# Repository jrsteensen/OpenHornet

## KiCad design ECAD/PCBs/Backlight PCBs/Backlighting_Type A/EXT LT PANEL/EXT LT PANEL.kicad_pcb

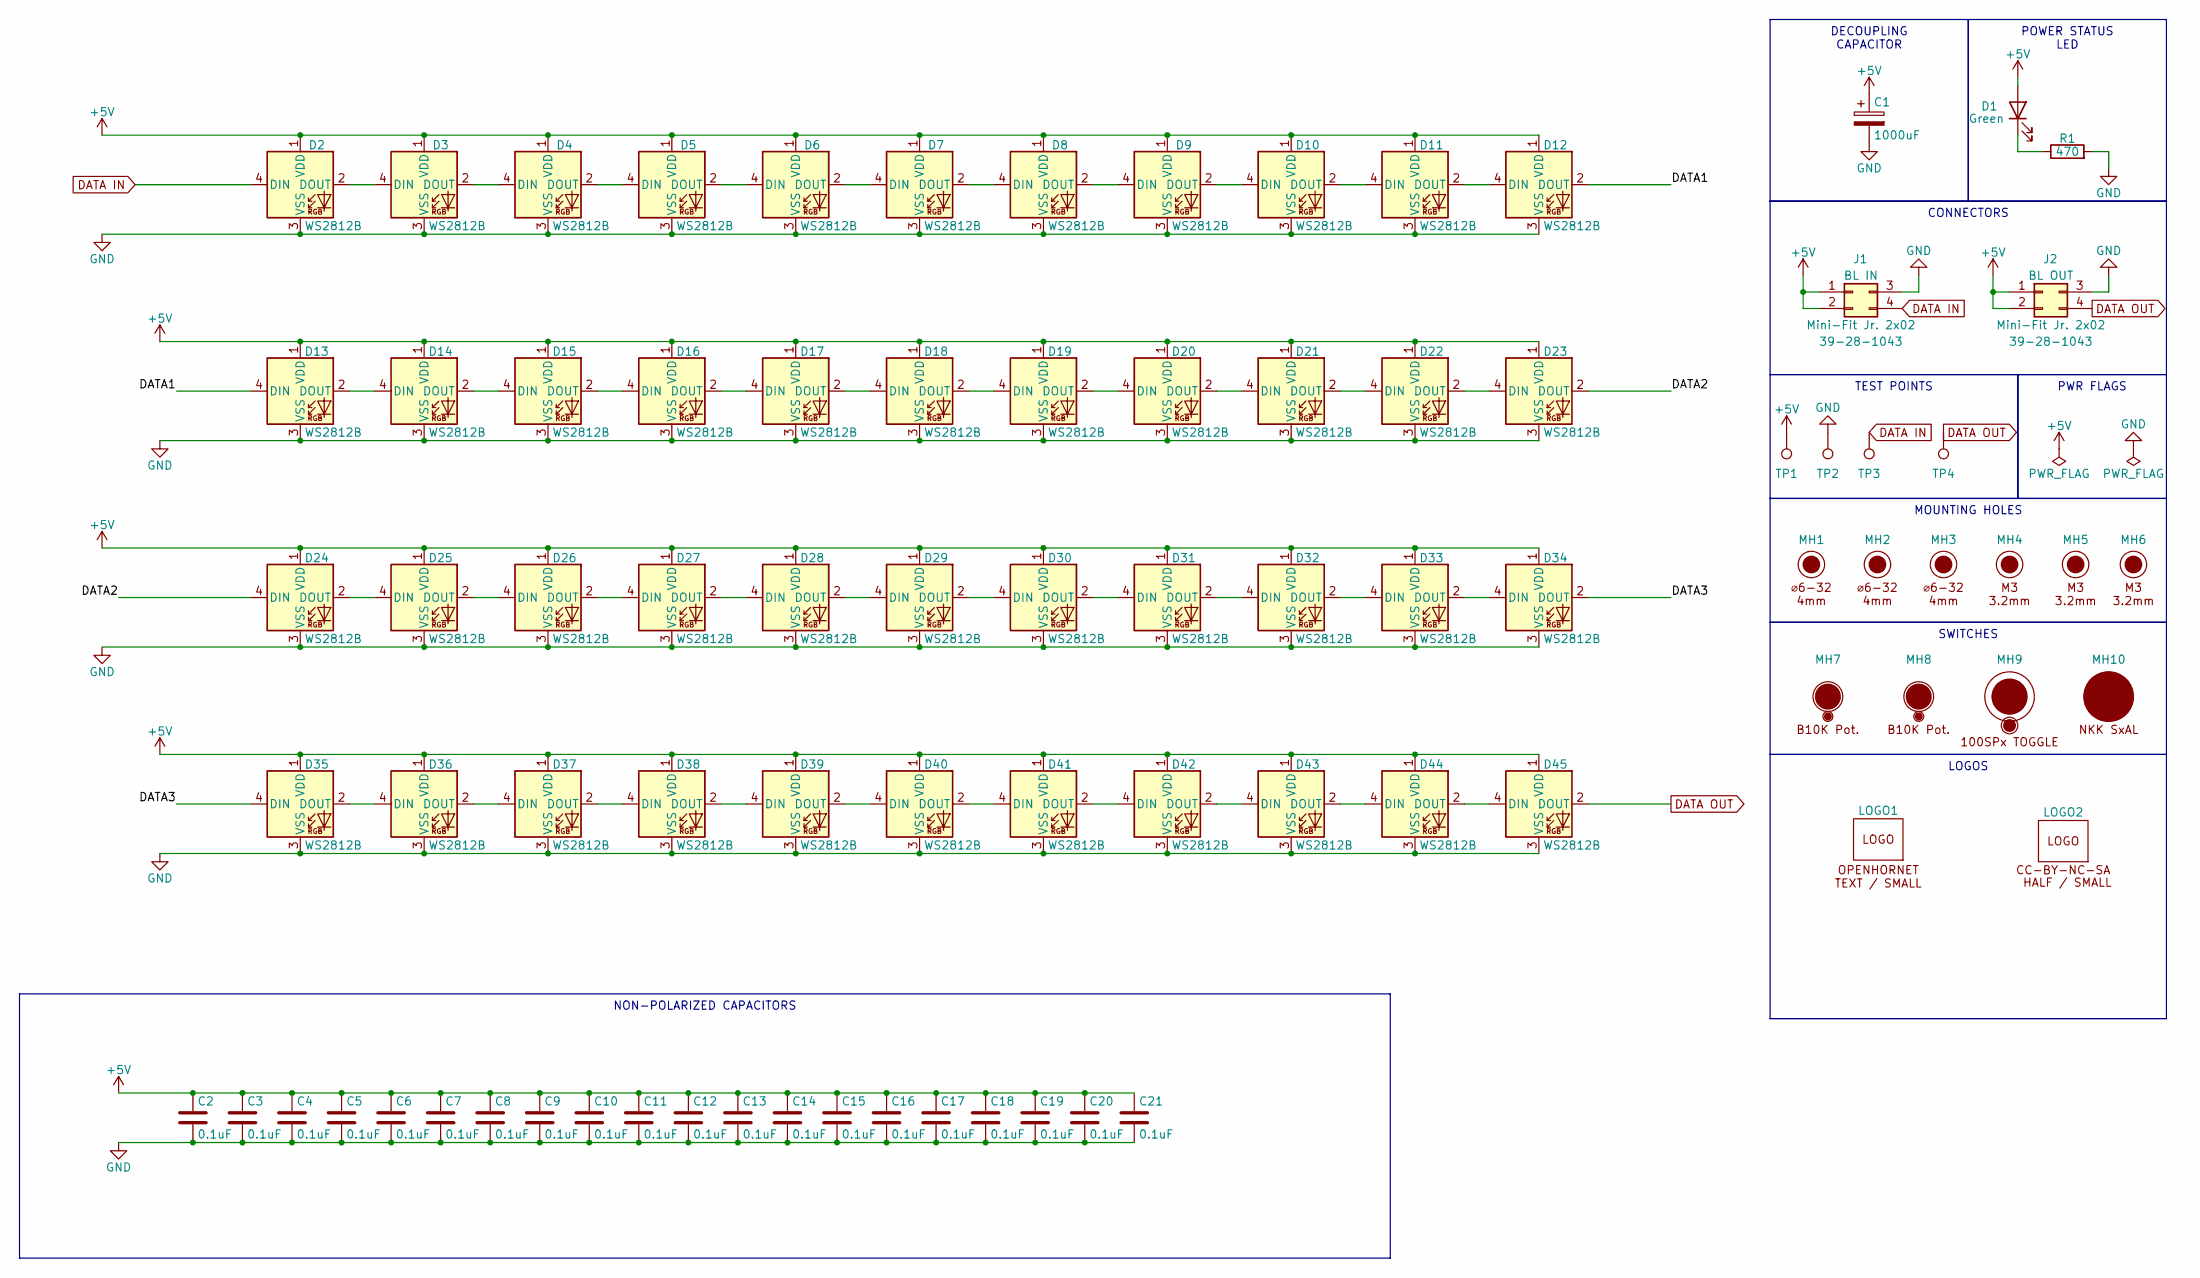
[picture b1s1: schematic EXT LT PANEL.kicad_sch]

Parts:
C1: 1000uF; CP_Elec_8x10; Manufacturer PN UWT0J102MNL1GS; LCSC C445083
C2, C3, C4, C5, C6, C7, C8, C9, C10, C11, C12, C13, C14, C15, C16, C17, C18, C19, C20, C21: 0.1uF; C_0603_1608Metric; Manufacturer PN CC0603KRX7R9BB104; LCSC C14663
D1: Green; LED_D3.0mm; Manufacturer PN 151031VS06000
D2, D3, D4, D5, D6, D7, D8, D9, D10, D11, D12, D13, D14, D15, D16, D17, D18, D19, D20, D21, D22, D23, D24, D25, D26, D27, D28, D29, D30, D31, D32, D33, D34, D35, D36, D37, D38, D39, D40, D41, D42, D43, D44, D45: WS2812B; LED_WS2812B_PLCC4_5.0x5.0mm_P3.2mm; Manufacturer PN WS2812B; LCSC C2761795
J1, J2: Mini-Fit Jr. 2x02; Molex_Mini-Fit_Jr_5566-04A_2x02_P4.20mm_Vertical; Manufacturer PN 39-28-1043; LCSC C293502
LOGO1: LOGO; LOGO_OH_Text_Small
LOGO2: LOGO; LOGO_CC-BY-NC-SA_Half_Small
MH1, MH2, MH3: 6x32 / 4mm; MountingHole_6-32_PHS
MH4, MH5, MH6: M3 / 3.2mm; MountingHole_3.2mm_M3_DIN965
MH7, MH8: Pot_B10K; BR10K_Pot_11mm_x_11mm; Manufacturer PN P0915N-FC20BR10K
MH9: Switch_100SPx; 100SPX_Toggle_13mm_x_18mm
MH10: Switch_NKK SxAL; SxAL_Toggle_13x13mm; Manufacturer PN SxAL
R1: 470; R_0603_1608Metric; Manufacturer PN 0603WAF4700T5E; LCSC C23179
TP1, TP2, TP3, TP4: TestPoint; TestPoint_THTPad_D1.5mm_Drill0.7mm

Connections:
+5V: C1.1, C2.1, C3.1, C4.1, C5.1, C6.1, C7.1, C8.1, C9.1, C10.1, C11.1, C12.1, C13.1, C14.1, C15.1, C16.1, C17.1, C18.1, C19.1, C20.1, C21.1, D1.2 (A), D2.1 (VDD), D3.1 (VDD), D4.1 (VDD), D5.1 (VDD), D6.1 (VDD), D7.1 (VDD), D8.1 (VDD), D9.1 (VDD), D10.1 (VDD), D11.1 (VDD), D12.1 (VDD), D13.1 (VDD), D14.1 (VDD), D15.1 (VDD), D16.1 (VDD), D17.1 (VDD), D18.1 (VDD), D19.1 (VDD), D20.1 (VDD), D21.1 (VDD), D22.1 (VDD), D23.1 (VDD), D24.1 (VDD), D25.1 (VDD), D26.1 (VDD), D27.1 (VDD), D28.1 (VDD), D29.1 (VDD), D30.1 (VDD), D31.1 (VDD), D32.1 (VDD), D33.1 (VDD), D34.1 (VDD), D35.1 (VDD), D36.1 (VDD), D37.1 (VDD), D38.1 (VDD), D39.1 (VDD), D40.1 (VDD), D41.1 (VDD), D42.1 (VDD), D43.1 (VDD), D44.1 (VDD), D45.1 (VDD), J1.1, J1.2 (Pin_3), J2.1, J2.2 (Pin_3), TP1.1
/DATA1: D12.2 (DOUT), D13.4 (DIN)
/DATA2: D23.2 (DOUT), D24.4 (DIN)
/DATA3: D34.2 (DOUT), D35.4 (DIN)
DATA IN: D2.4 (DIN), J1.4, TP3.1
DATA OUT: D45.2 (DOUT), J2.4, TP4.1
GND: C1.2, C2.2, C3.2, C4.2, C5.2, C6.2, C7.2, C8.2, C9.2, C10.2, C11.2, C12.2, C13.2, C14.2, C15.2, C16.2, C17.2, C18.2, C19.2, C20.2, C21.2, D2.3 (VSS), D3.3 (VSS), D4.3 (VSS), D5.3 (VSS), D6.3 (VSS), D7.3 (VSS), D8.3 (VSS), D9.3 (VSS), D10.3 (VSS), D11.3 (VSS), D12.3 (VSS), D13.3 (VSS), D14.3 (VSS), D15.3 (VSS), D16.3 (VSS), D17.3 (VSS), D18.3 (VSS), D19.3 (VSS), D20.3 (VSS), D21.3 (VSS), D22.3 (VSS), D23.3 (VSS), D24.3 (VSS), D25.3 (VSS), D26.3 (VSS), D27.3 (VSS), D28.3 (VSS), D29.3 (VSS), D30.3 (VSS), D31.3 (VSS), D32.3 (VSS), D33.3 (VSS), D34.3 (VSS), D35.3 (VSS), D36.3 (VSS), D37.3 (VSS), D38.3 (VSS), D39.3 (VSS), D40.3 (VSS), D41.3 (VSS), D42.3 (VSS), D43.3 (VSS), D44.3 (VSS), D45.3 (VSS), J1.3 (Pin_2), J2.3 (Pin_2), R1.2, TP2.1
unnamed: D1.1 (K), R1.1
unnamed: D2.2 (DOUT), D3.4 (DIN)
unnamed: D3.2 (DOUT), D4.4 (DIN)
unnamed: D4.2 (DOUT), D5.4 (DIN)
unnamed: D5.2 (DOUT), D6.4 (DIN)
unnamed: D6.2 (DOUT), D7.4 (DIN)
unnamed: D7.2 (DOUT), D8.4 (DIN)
unnamed: D8.2 (DOUT), D9.4 (DIN)
unnamed: D9.2 (DOUT), D10.4 (DIN)
unnamed: D10.2 (DOUT), D11.4 (DIN)
unnamed: D11.2 (DOUT), D12.4 (DIN)
unnamed: D13.2 (DOUT), D14.4 (DIN)
unnamed: D14.2 (DOUT), D15.4 (DIN)
unnamed: D15.2 (DOUT), D16.4 (DIN)
unnamed: D16.2 (DOUT), D17.4 (DIN)
unnamed: D17.2 (DOUT), D18.4 (DIN)
unnamed: D18.2 (DOUT), D19.4 (DIN)
unnamed: D19.2 (DOUT), D20.4 (DIN)
unnamed: D20.2 (DOUT), D21.4 (DIN)
unnamed: D21.2 (DOUT), D22.4 (DIN)
unnamed: D22.2 (DOUT), D23.4 (DIN)
unnamed: D24.2 (DOUT), D25.4 (DIN)
unnamed: D25.2 (DOUT), D26.4 (DIN)
unnamed: D26.2 (DOUT), D27.4 (DIN)
unnamed: D27.2 (DOUT), D28.4 (DIN)
unnamed: D28.2 (DOUT), D29.4 (DIN)
unnamed: D29.2 (DOUT), D30.4 (DIN)
unnamed: D30.2 (DOUT), D31.4 (DIN)
unnamed: D31.2 (DOUT), D32.4 (DIN)
unnamed: D32.2 (DOUT), D33.4 (DIN)
unnamed: D33.2 (DOUT), D34.4 (DIN)
unnamed: D35.2 (DOUT), D36.4 (DIN)
unnamed: D36.2 (DOUT), D37.4 (DIN)
unnamed: D37.2 (DOUT), D38.4 (DIN)
unnamed: D38.2 (DOUT), D39.4 (DIN)
unnamed: D39.2 (DOUT), D40.4 (DIN)
unnamed: D40.2 (DOUT), D41.4 (DIN)
unnamed: D41.2 (DOUT), D42.4 (DIN)
unnamed: D42.2 (DOUT), D43.4 (DIN)
unnamed: D43.2 (DOUT), D44.4 (DIN)
unnamed: D44.2 (DOUT), D45.4 (DIN)

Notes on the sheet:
DECOUPLING CAPACITOR
TEST POINTS
POWER STATUS LED
NON-POLARIZED CAPACITORS
PWR FLAGS
SWITCHES
CONNECTORS
LOGOS
MOUNTING HOLES

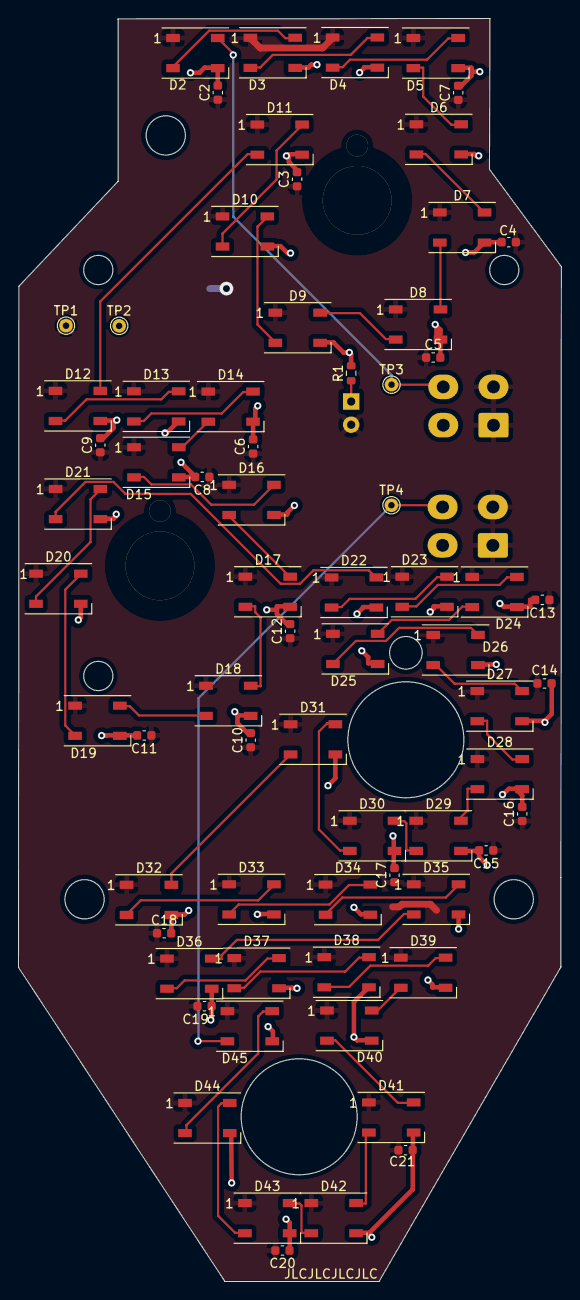
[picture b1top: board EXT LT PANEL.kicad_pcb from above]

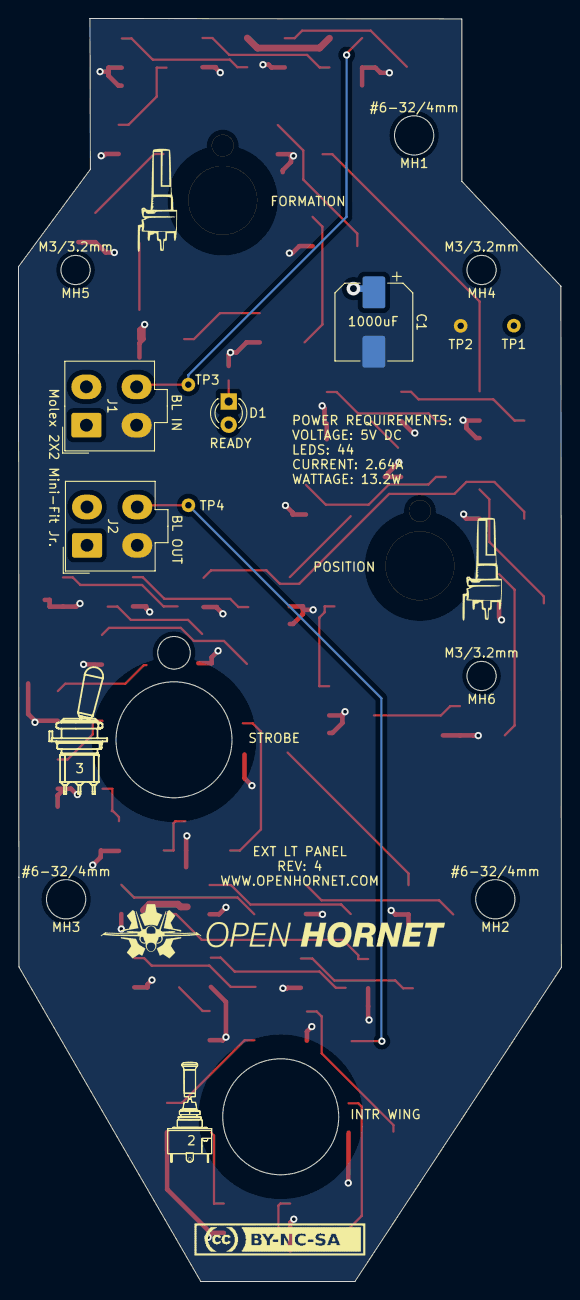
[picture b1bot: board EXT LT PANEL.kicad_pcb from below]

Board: 2 copper layers, 59.4 x 138.3 mm, 89 parts (16 on the bottom side), 48 nets.

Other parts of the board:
LOGO3, LOGO4: LOGO; BR10KPot
LOGO5: LOGO; 100SP3_Toggle_Silkscreen
LOGO6: LOGO; S2AL_Toggle_Silkscreen

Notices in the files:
ECAD/PCBs/Backlight PCBs/Backlighting_Type A/EXT LT PANEL/EXT LT PANEL.kicad_pcb:
License: CC BY-NC-SA
parts and their libraries:
https://creativecommons.org/licenses/by-nc-sa/4.0
